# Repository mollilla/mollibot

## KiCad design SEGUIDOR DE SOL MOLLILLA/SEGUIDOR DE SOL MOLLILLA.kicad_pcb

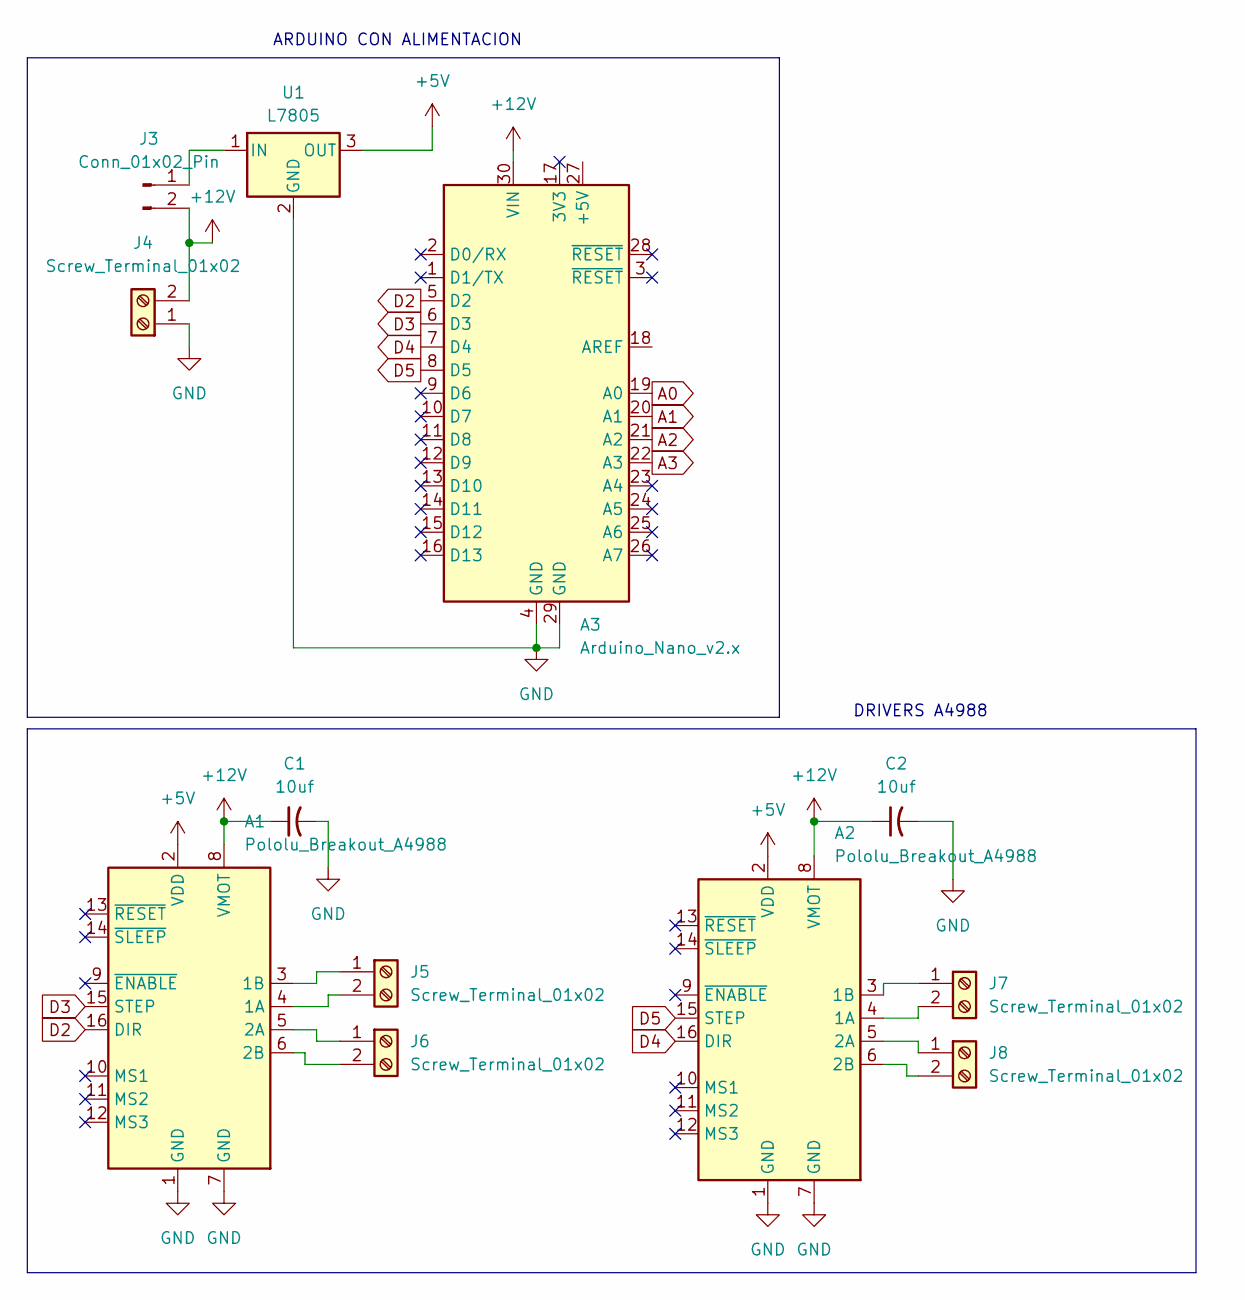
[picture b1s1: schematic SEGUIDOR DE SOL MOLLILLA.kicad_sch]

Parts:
A1, A2: Pololu_Breakout_A4988; DRV8825
A3: Arduino_Nano_v2.x; arduino_nano_header
C1, C2: 10uf; CAP_ELEC_5x11mm
J3: Conn_01x02_Pin; PinHeader_1x02_P2.54mm_Vertical
J4, J5, J6, J7, J8: Screw_Terminal_01x02; BORNERA2_AZUL
U1: L7805; TO-220-2

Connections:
+5V: A1.2 (VDD), A2.2 (VDD), U1.3 (OUT)
+12V: A1.8 (VMOT), A2.8 (VMOT), A3.30 (VIN), C1.1, C2.1, J3.2, J4.2
A0: A3.19 (A0)
A1: A3.20 (A1)
A2: A3.21 (A2)
A3: A3.22 (A3)
D2: A1.16 (DIR), A3.5 (D2)
D3: A1.15 (STEP), A3.6 (D3)
D4: A2.16 (DIR), A3.7 (D4)
D5: A2.15 (STEP), A3.8 (D5)
GND: A1.1 (GND), A1.7 (GND), A2.1 (GND), A2.7 (GND), A3.4 (GND), A3.29 (GND), C1.2, C2.2, J4.1, U1.2 (GND)
unnamed: A1.4 (1A), J5.2
unnamed: A1.3 (1B), J5.1
unnamed: A1.5 (2A), J6.1
unnamed: A1.6 (2B), J6.2
unnamed: A2.4 (1A), J7.2
unnamed: A2.3 (1B), J7.1
unnamed: A2.5 (2A), J8.1
unnamed: A2.6 (2B), J8.2
unnamed: J3.1, U1.1 (IN)

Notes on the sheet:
DRIVERS A4988
ARDUINO CON ALIMENTACION

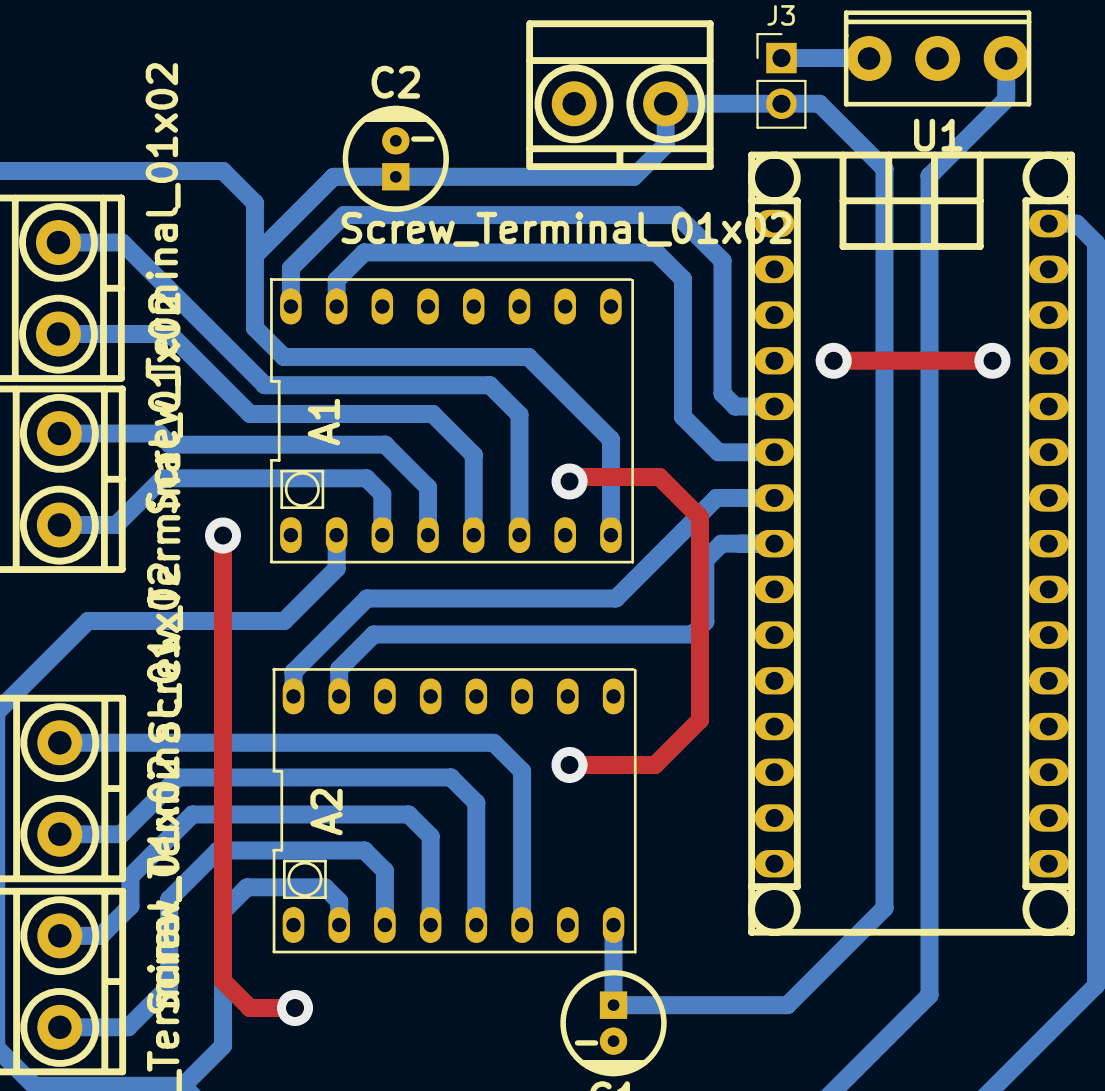
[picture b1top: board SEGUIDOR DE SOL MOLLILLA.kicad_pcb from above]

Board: 2 copper layers, 12 parts (0 on the bottom side), 16 nets.

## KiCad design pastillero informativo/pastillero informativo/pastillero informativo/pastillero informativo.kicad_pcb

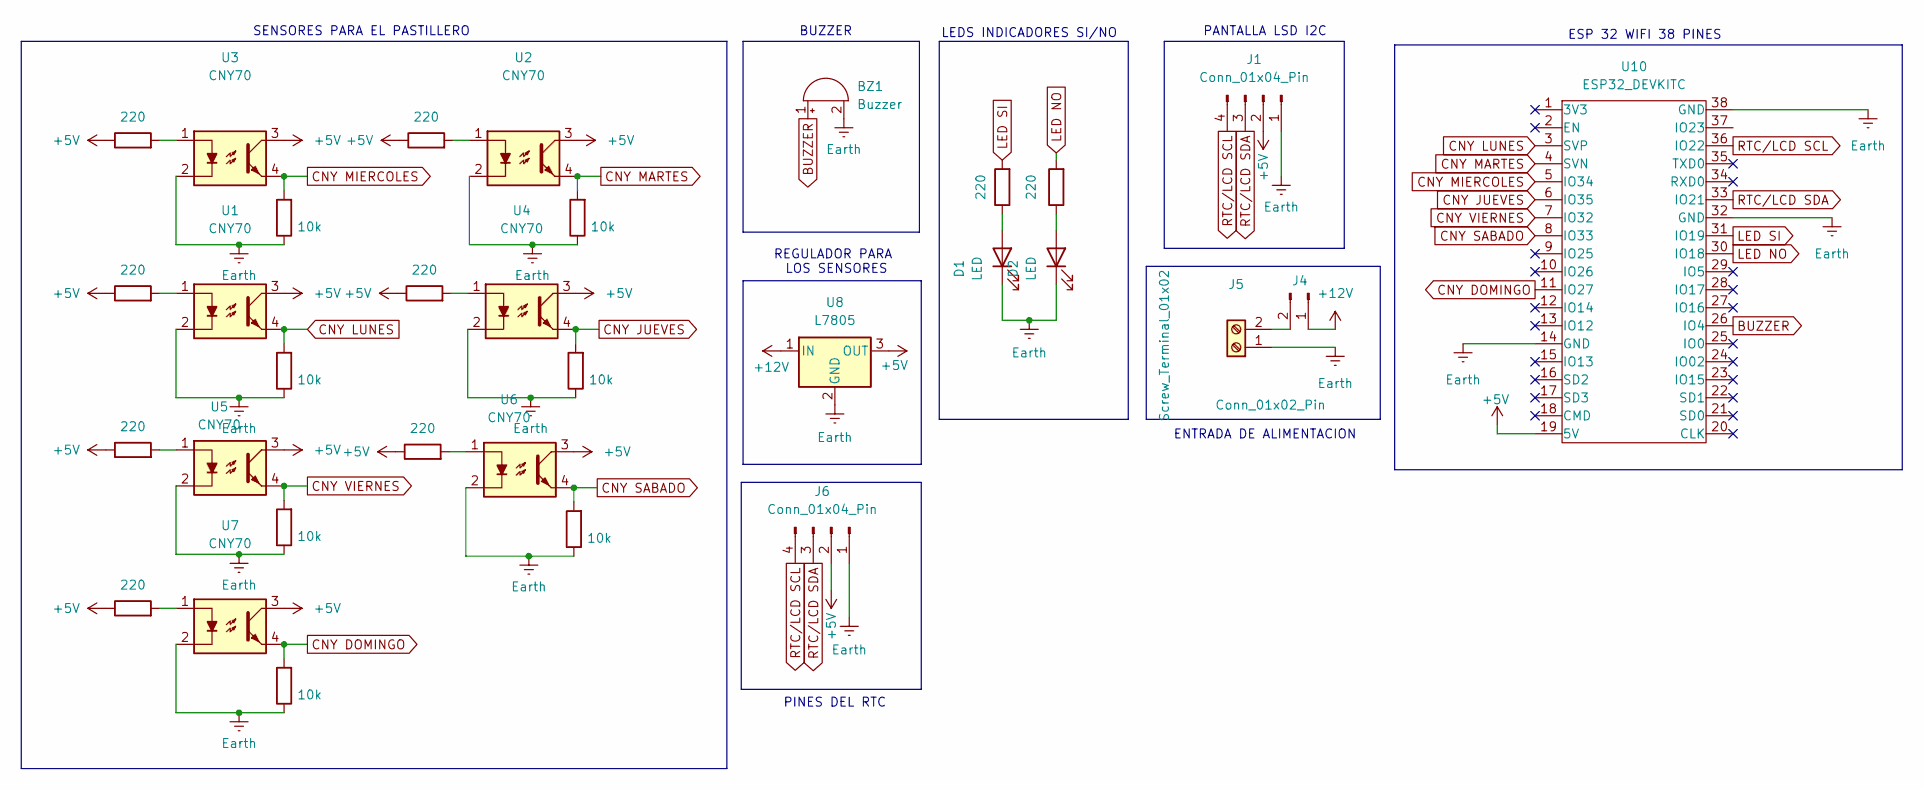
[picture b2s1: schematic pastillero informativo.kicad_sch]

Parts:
BZ1: Buzzer; Buzzer_TDK_PS1240P02BT_D12.2mm_H6.5mm
D1, D2: LED; LED_D3.0mm
J1, J6: Conn_01x04_Pin; PinHeader_1x04_P2.54mm_Vertical
J4: Conn_01x02_Pin; PinHeader_1x02_P2.54mm_Vertical
J5: Screw_Terminal_01x02; TerminalBlock_MaiXu_MX126-5.0-02P_1x02_P5.00mm
R1, R2, R12, R14, R16, R18, R20, R22, R23: 220; LED_0805_2012Metric
R11, R13, R15, R17, R19, R21, R24: 10k; LED_0805_2012Metric
U1, U2, U3, U4, U5, U6, U7: CNY70; PinHeader_1x04_P2.54mm_Vertical
U8: L7805; TO-263-3_TabPin2
U10: ESP32_DEVKITC

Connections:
+5V: J1.2, J6.2, R12.1, R14.1, R16.1, R18.1, R20.1, R22.1, R23.1, U1.3, U2.3, U3.3, U4.3, U5.3, U6.3, U7.3, U8.3 (OUT), U10.19 (5V)
+12V: J4.1, U8.1 (IN)
BUZZER: BZ1.1 (-), U10.26 (IO4)
CNY DOMINGO: R17.2, U7.4, U10.11 (IO27)
CNY JUEVES: R13.2, U4.4, U10.6 (IO35)
CNY LUNES: R21.2, U1.4, U10.3 (SVP)
CNY MARTES: R11.2, U2.4, U10.4 (SVN)
CNY MIERCOLES: R24.2, U3.4, U10.5 (IO34)
CNY SABADO: R15.2, U6.4, U10.8 (IO33)
CNY VIERNES: R19.2, U5.4, U10.7 (IO32)
Earth: BZ1.2 (+), D1.1 (K), D2.1 (K), J1.1, J5.1, J6.1, R11.1, R13.1, R15.1, R17.1, R19.1, R21.1, R24.1, U1.2, U2.2, U3.2, U4.2, U5.2, U6.2, U7.2, U8.2 (GND), U10.14 (GND), U10.32 (GND), U10.38 (GND)
LED NO: R2.2, U10.30 (IO18)
LED SI: R1.2, U10.31 (IO19)
unnamed: D1.2 (A), R1.1
unnamed: D2.2 (A), R2.1
unnamed: J4.2, J5.2
unnamed: R12.2, U3.1
unnamed: R14.2, U2.1
unnamed: R16.2, U1.1
unnamed: R18.2, U4.1
unnamed: R20.2, U5.1
unnamed: R22.2, U7.1
unnamed: R23.2, U6.1
RTC/LCD SCL: J1.4, J6.4, U10.36 (IO22)
RTC/LCD SDA: J1.3, J6.3, U10.33 (IO21)

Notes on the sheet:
ESP 32 WIFI 38 PINES
ENTRADA DE ALIMENTACION
PANTALLA LSD I2C
PINES DEL RTC
SENSORES PARA EL PASTILLERO
REGULADOR PARA LOS SENSORES
BUZZER
LEDS INDICADORES SI/NO

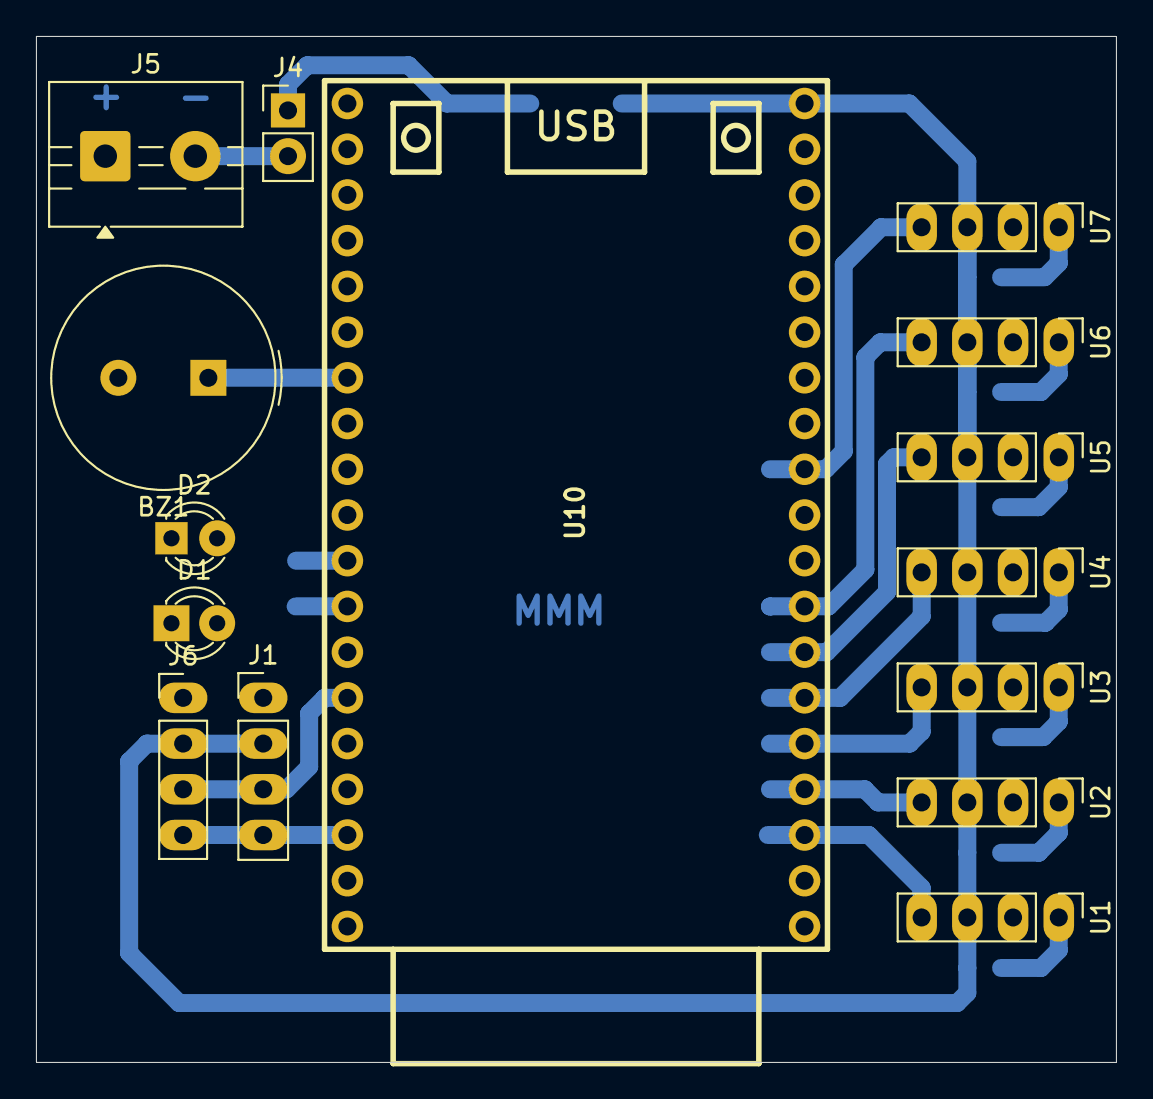
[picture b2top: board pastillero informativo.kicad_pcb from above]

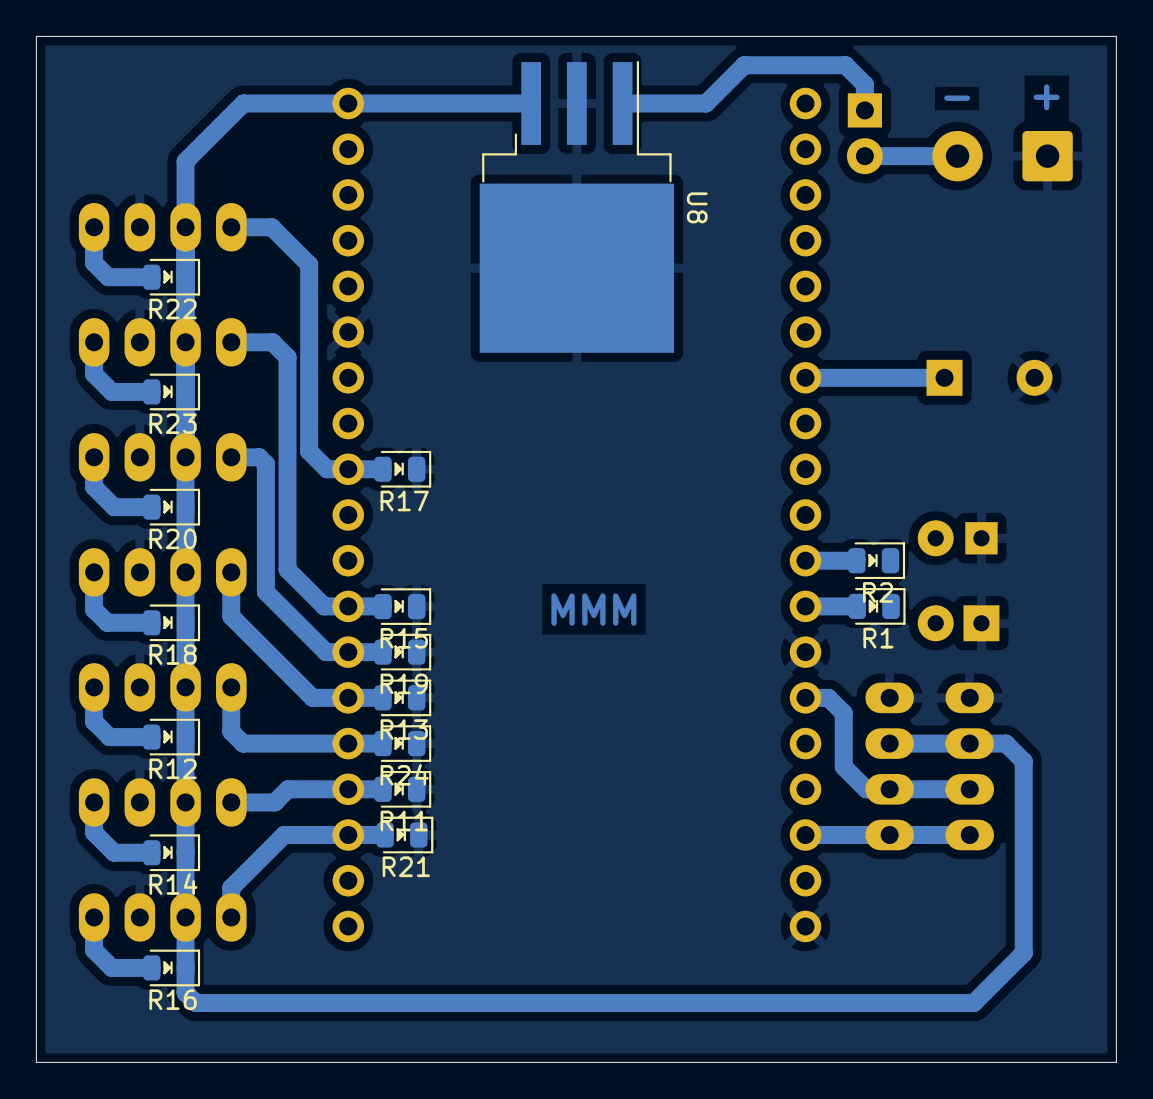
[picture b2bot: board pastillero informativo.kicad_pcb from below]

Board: 2 copper layers, 60.0 x 57.0 mm, 32 parts (17 on the bottom side), 25 nets.

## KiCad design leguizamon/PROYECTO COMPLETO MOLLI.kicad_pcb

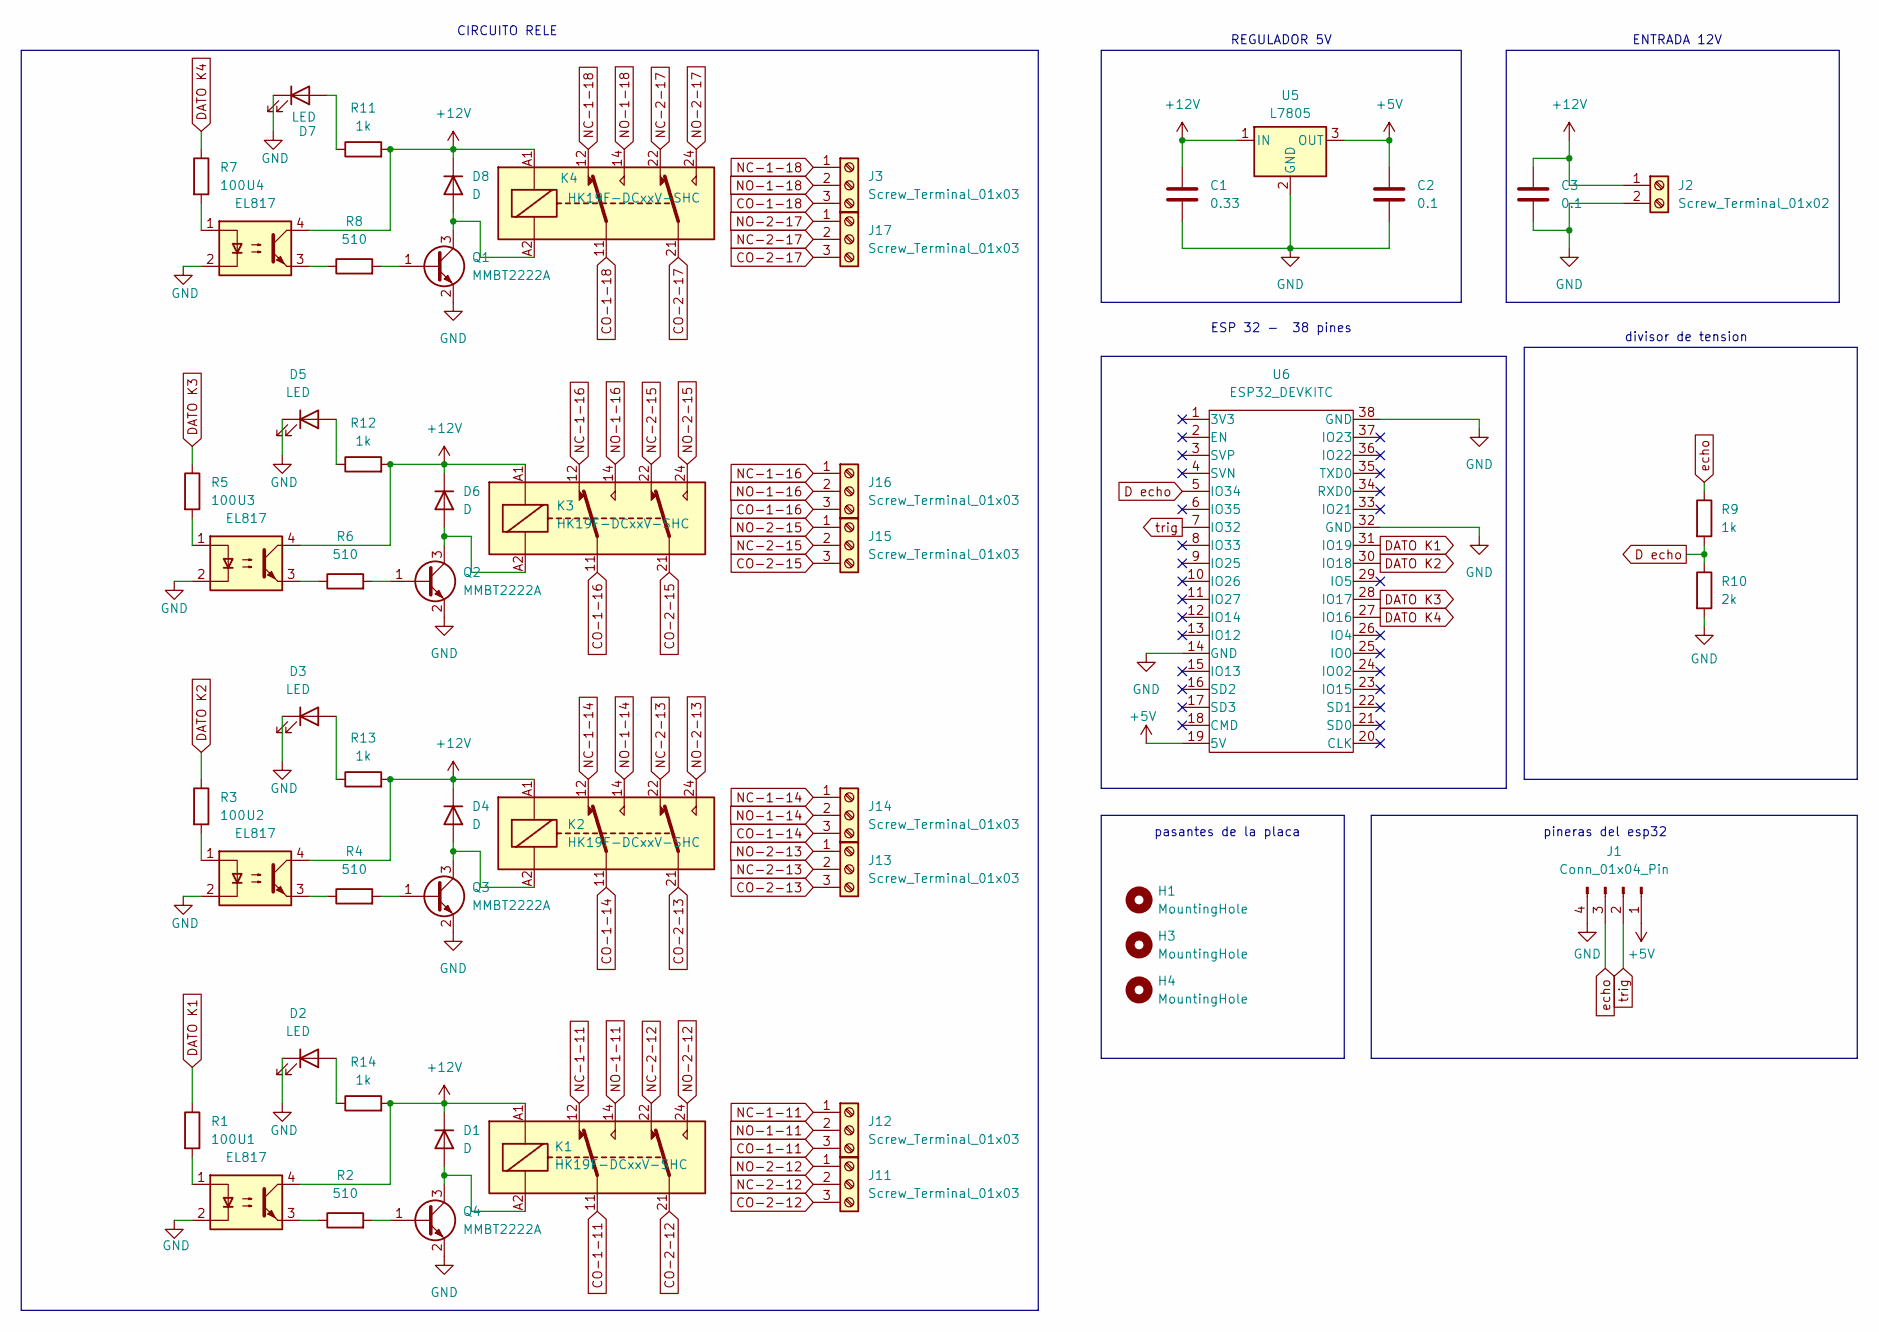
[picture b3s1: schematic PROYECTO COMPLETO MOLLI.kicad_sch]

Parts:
C1: 0.33; C_0805_2012Metric
C2: 0.1; C_0805_2012Metric
C3: 0.1; C_Radial_D5.0mm_H5.0mm_P2.00mm
D1, D4, D6, D8: D; D_SMA
D2, D3, D5, D7: LED; LED_0805_2012Metric
H1, H3, H4: MountingHole; MountingHole_2.1mm
J1: Conn_01x04_Pin; PinHeader_1x04_P2.54mm_Vertical
J2: Screw_Terminal_01x02; TerminalBlock_MaiXu_MX126-5.0-02P_1x02_P5.00mm
J3, J11, J12, J13, J14, J15, J16, J17: Screw_Terminal_01x03; TerminalBlock_Xinya_XY308-2.54-3P_1x03_P2.54mm_Horizontal
K1, K2, K3, K4: HK19F-DCxxV-SHC; Relay_DPDT_Finder_30.22
Q1, Q2, Q3, Q4: MMBT2222A; SOT-23
R1, R3, R5, R7: 100; R_0805_2012Metric
R2, R4, R6, R8: 510; R_0805_2012Metric
R9: 1k; R_Axial_DIN0204_L3.6mm_D1.6mm_P7.62mm_Horizontal
R10: 2k; R_Axial_DIN0204_L3.6mm_D1.6mm_P7.62mm_Horizontal
R11, R12, R13, R14: 1k; R_0805_2012Metric
U1, U2, U3, U4: EL817; DIP-4_W7.62mm
U5: L7805; TO-263-3_TabPin2
U6: ESP32_DEVKITC; ESP32S

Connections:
+5V: C2.1, J1.1, U5.3 (OUT), U6.19 (5V)
+12V: C1.1, C3.1, D1.1 (K), D4.1 (K), D6.1 (K), D8.1 (K), J2.1, K1.A1, K2.A1, K3.A1, K4.A1, R11.2, R12.2, R13.2, R14.2, U1.4, U2.4, U3.4, U4.4, U5.1 (IN)
CO-1-11: J12.3, K1.11
CO-1-14: J14.3, K2.11
CO-1-16: J16.3, K3.11
CO-1-18: J3.3, K4.11
CO-2-12: J11.3, K1.21
CO-2-13: J13.3, K2.21
CO-2-15: J15.3, K3.21
CO-2-17: J17.3, K4.21
D echo: R9.2, R10.1, U6.5 (IO34)
DATO K1: R1.1, U6.31 (IO19)
DATO K2: R3.1, U6.30 (IO18)
DATO K3: R5.1, U6.28 (IO17)
DATO K4: R7.1, U6.27 (IO16)
GND: C1.2, C2.2, C3.2, D2.1 (K), D3.1 (K), D5.1 (K), D7.1 (K), J1.4, J2.2, Q1.2 (E), Q2.2 (E), Q3.2 (E), Q4.2 (E), R10.2, U1.2, U2.2, U3.2, U4.2, U5.2 (GND), U6.14 (GND), U6.32 (GND), U6.38 (GND)
NC-1-11: J12.1, K1.12
NC-1-14: J14.1, K2.12
NC-1-16: J16.1, K3.12
NC-1-18: J3.1, K4.12
NC-2-12: J11.2, K1.22
NC-2-13: J13.2, K2.22
NC-2-15: J15.2, K3.22
NC-2-17: J17.2, K4.22
NO-1-11: J12.2, K1.14
NO-1-14: J14.2, K2.14
NO-1-16: J16.2, K3.14
NO-1-18: J3.2, K4.14
NO-2-12: J11.1, K1.24
NO-2-13: J13.1, K2.24
NO-2-15: J15.1, K3.24
NO-2-17: J17.1, K4.24
unnamed: D1.2 (A), K1.A2, Q4.3 (C)
unnamed: D2.2 (A), R14.1
unnamed: D3.2 (A), R13.1
unnamed: D4.2 (A), K2.A2, Q3.3 (C)
unnamed: D5.2 (A), R12.1
unnamed: D6.2 (A), K3.A2, Q2.3 (C)
unnamed: D7.2 (A), R11.1
unnamed: D8.2 (A), K4.A2, Q1.3 (C)
unnamed: Q1.1 (B), R8.2
unnamed: Q2.1 (B), R6.2
unnamed: Q3.1 (B), R4.2
unnamed: Q4.1 (B), R2.2
unnamed: R1.2, U1.1
unnamed: R2.1, U1.3
unnamed: R3.2, U2.1
unnamed: R4.1, U2.3
unnamed: R5.2, U3.1
unnamed: R6.1, U3.3
unnamed: R7.2, U4.1
unnamed: R8.1, U4.3
echo: J1.3, R9.1
trig: J1.2, U6.7 (IO32)

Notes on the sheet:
ESP 32 - 38 pines
ENTRADA 12V
pasantes de la placa
CIRCUITO RELE
REGULADOR 5V
divisor de tension
pineras del esp32

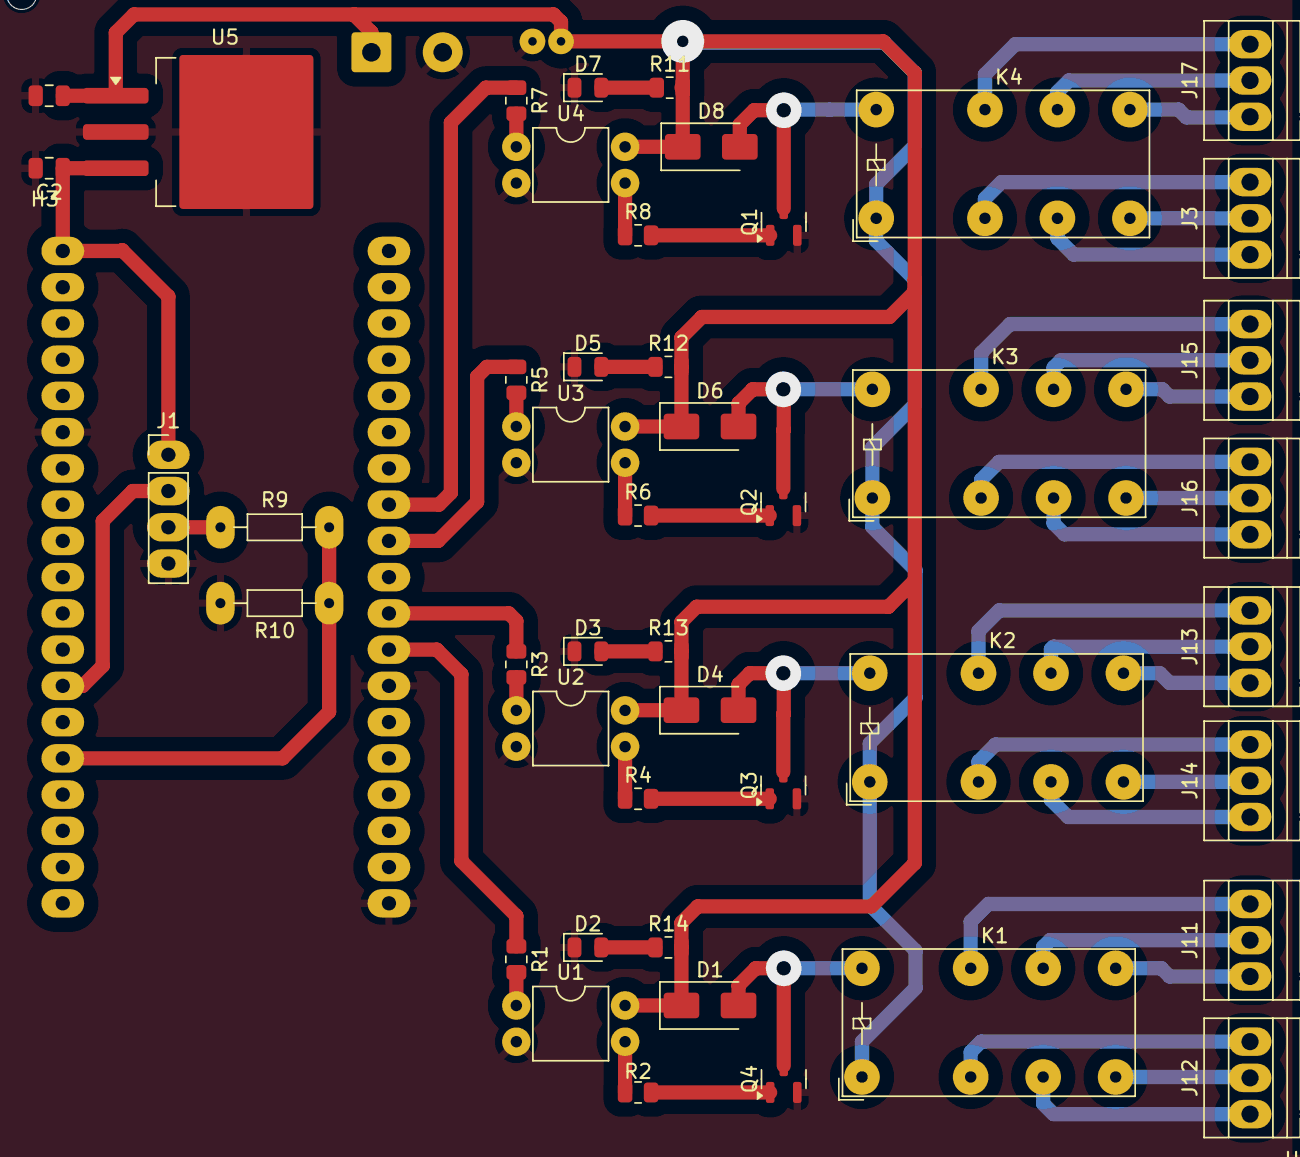
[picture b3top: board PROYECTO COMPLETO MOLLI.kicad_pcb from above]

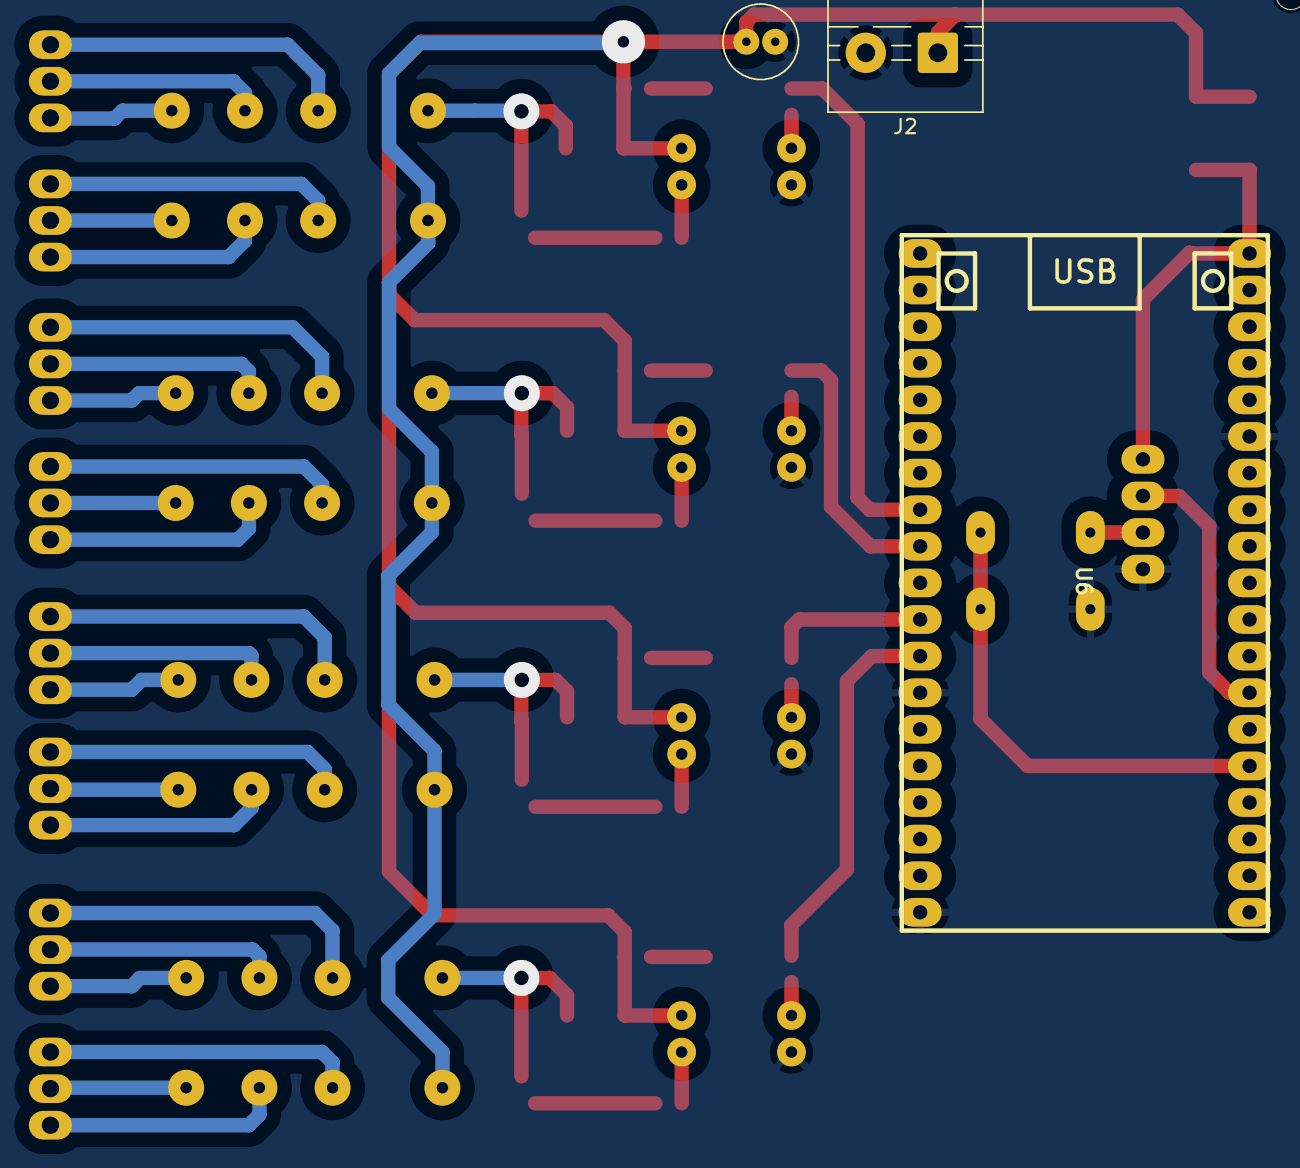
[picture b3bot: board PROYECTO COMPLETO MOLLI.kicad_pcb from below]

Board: 2 copper layers, 52 parts (3 on the bottom side), 54 nets.

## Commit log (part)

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2025-03-28 Mi primer commit
2025-03-28 Modificamos titulo en index.html
2025-03-28 se agregaron las carpetas
2025-03-28 se arreglaron las carpetas
2025-03-28 Se borro txt
2025-03-28 Se agrego la carpeta Kicad
2025-06-03 Add files via upload
    3/6/25 pcb terminado
2025-06-06 Add files via upload
    6/6
2025-06-06 Add files via upload
    arregle
2026-05-21 pastillero 21/5/26
2026-05-21 cambio de pads
